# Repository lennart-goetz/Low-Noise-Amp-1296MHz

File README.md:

# 1.3 GHz Low-Noise Amplifier Front-End

This repository contains the design files for a finished and RF-characterized 1.3 GHz low-noise amplifier front-end intended for weak-signal reception, especially Earth-Moon-Earth (EME) operation in the 23 cm amateur radio band.

The project includes a low-noise amplifier, a high-power Bias-T concept, PCB production files, schematics, mechanical drawings, and measurement results. The goal of this repository is to make the design reproducible and to give RF engineers a realistic impression of the measured performance.

## Overview

The front-end is designed for operation around **1.3 GHz** and consists mainly of:

- a two-stage **low-noise amplifier** with integrated band-pass filtering,
- a compact **Bias-T** for remote supply and high-power RF path requirements,
- system-level integration for a transmit/receive front-end,
- mechanical mounting and enclosure concept.

The LNA is optimized for low noise figure and sufficient gain directly at the antenna side of the receive chain. The Bias-T was designed with low insertion loss and a high RF power target in mind.

## Measured Performance

The following values summarize the characterized final design at approximately **1.3 GHz**.

| Module | Parameter | Measured result |
|---|---:|---:|
| LNA | Gain | **30.57 dB** |
| LNA | Noise figure | **0.47 dB** |
| LNA | Input return loss, S11 | **-9.7 dB** |
| LNA | Output return loss, S22 | **-11.1 dB** |
| LNA | IIP3 | **-8.63 dBm** |
| Bias-T | Insertion loss | **0.45 dB** |
| Bias-T | Input/output matching | **< -15 dB** in the useful band |
| Bias-T | RF power design target | **500 W CW** |

The LNA achieves a sub-0.5 dB noise figure together with roughly 30 dB gain, making it suitable as the first active stage in a low-noise receive system. The integrated filtering improves out-of-band suppression compared with a broadband amplifier-only approach.

## Hardware

### Low-Noise Amplifier

The final LNA PCB is a compact RF board for 1.3 GHz operation. It uses microstrip matching and an integrated band-pass filter. The released production files are intended to allow the board to be manufactured and assembled reproducibly.

### Bias-T

The Bias-T provides DC injection while maintaining a low-loss RF path. The final version uses an RF choke approach instead of a quarter-wave stub to reduce board size and improve broadband behavior.

## Repository Contents

Important files for reproduction are located in `ok_git/`:

- `ok_git/LNA_V2_gerber.zip` – final LNA PCB production files
- `ok_git/Bias_T_V2_gerber.zip` – final Bias-T PCB production files
- `ok_git/schematic.pdf` – system schematic
- `ok_git/mechanik/` – mechanical drawings and enclosure-related files
- `ok_git/images/` – photos, renderings, and measurement screenshots

Earlier prototype files are also included for reference.

## Reproduction Notes

- The design targets the 1.3 GHz / 23 cm band.
- Keep RF input interconnects as short and low-loss as possible, especially before the LNA input.
- Use suitable RF connectors, coaxial cables, and enclosure grounding for repeatable results.
- For the Bias-T, verify thermal behavior and voltage margins for the intended transmit power and duty cycle in the final installation.
- After assembly, characterize S-parameters and noise figure before using the module in a receive chain.

## License

No explicit license information is included in this repository yet. Please contact the author before using the design commercially or redistributing modified versions.

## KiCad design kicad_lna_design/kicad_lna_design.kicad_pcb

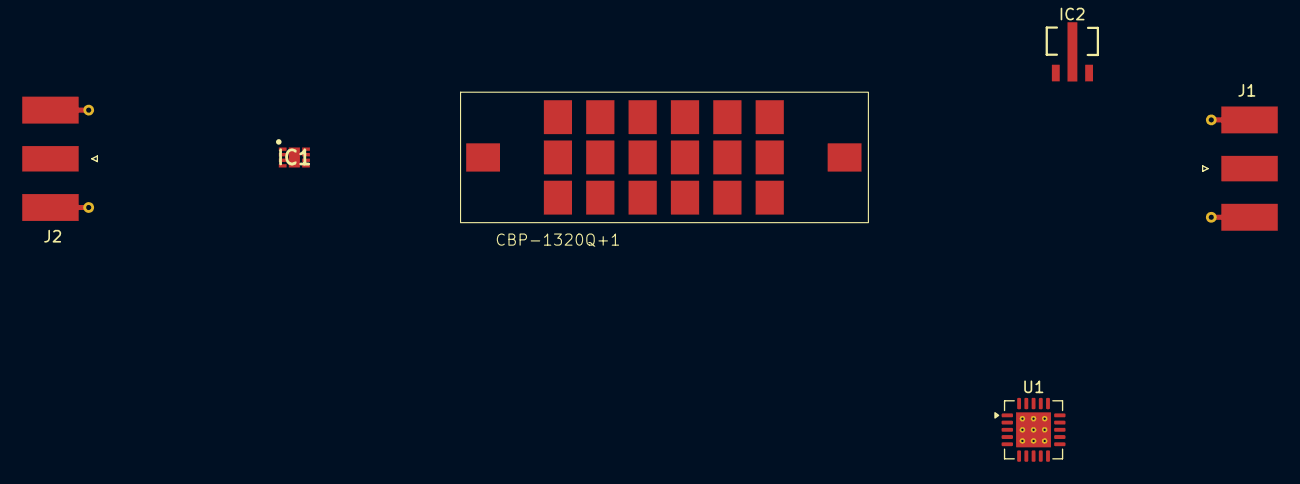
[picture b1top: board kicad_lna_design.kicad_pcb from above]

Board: 2 copper layers, 6 parts (0 on the bottom side), 5 nets, no tracks yet.

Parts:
CBP-1320Q+1: cbp-1320Q+
IC1: SKY67151-396LF
IC2: pga-103+
J1, J2: Conn_Coaxial; SMA_Molex_73251-1153_EdgeMount_Horizontal
U1: TPS7A4701xRGW; Texas_RGW0020A_VQFN-20-1EP_5x5mm_P0.65mm_EP3.15x3.15mm_Ther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

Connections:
GND: CBP-1320Q+1.3 (gnd), IC2.2 (GND), J1.2 (Ext), J2.2 (Ext)
unnamed: CBP-1320Q+1.2 (Out), IC2.1 (IN)
unnamed: IC2.3 (OUT/DC), J2.1 (In)
unnamed: U1.15 (IN), U1.16 (IN)
unnamed: U1.1 (OUT), U1.20 (OUT)

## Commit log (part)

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2026-03-16 chore: apply .gitignore and remove unnecessary binaries/backups from tracking
2026-03-17 news for the HF Relais
2026-03-17 updated mechanical planning
2026-03-24 updates schematic and pcb Design
2026-03-24 changes structure
2026-03-26 added production data for pcb
2026-03-26 added production files for PCB
2026-03-27 changed prod files
2026-04-05 added photo
2026-04-23 LNA V1 assembled photos
2026-04-23 added gerber files
2026-04-28 LNA V2 prod data
2026-04-28 added schematic
2026-05-17 LNA V2 photos
2026-05-17 Bias-T connection test
2026-06-01 Bias-T V2 Photo
2026-06-01 Bias-T V2 real Photo
2026-06-01 added prod files
